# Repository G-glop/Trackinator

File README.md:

# Todo

- [X] Put Obsidian notes inside the repo
- [X] Add a README.md
- [x] Search the calendar for any Trackinator info and add it here
	- [x] select the flex connector & crystals & oscillators (to free up browser tabs)
	- [x] transfer my eyetrack diagram to kicad (don't worry about simple component values/choices)
	- [x] abandon fully flex design and opt into frunkable + flex illuminators / extensions
	- [ ] drive all ir leds from a single current limited source to ensure sum i <= safe limit
- [ ] M.2 like half screw-hole for mounting in a custom frunk housing
- [x] Import new FFC connector
- FCC connector orientaion:
	- Face cams prefer pins up
	- Eye and nose cams prefer pins down
- [ ] Place the hub indicator LEDs close to their respective ESP/downstream port
- [ ] ESP UART output headers
- [x] Remove `fp-info-cache` from the repo and ignore it
- [x] Add camera pinout to it
	- Did the option with least fewest crossing lines, could've copied the xiao but eh
- [ ] Symmetrize all the connectors and lock them
- [x] Select and add USB C and A female connectors
  - [ ] What does a USB C host port need in addition to P+N+5V+GND?
- [x] 3D print the outline + USB A + FFC connectors to check the fit
- [ ] Switch KiCad to JLCPCB 4+ layer capabilites (I'm gonna need them)
- [ ] Use painters tape + scanner + 3d printer to prototype a flex PCB (or 3D scan / manally model the index)
  - [ ] IR illumination
  - [ ] Ambilight
  - [ ] Reuse the 24P FFC connector
	  - Either look at the [camera mechanical drawings](https://www.aliexpress.com/item/1005003906449317.html?spm=a2g0o.order_list.order_list_main.10.361c1802tWpc3p) or at the [FFC connector datasheet](https://datasheet.lcsc.com/lcsc/2001071406_XFCN-F0503-ZV-24-20T-R_C481246.pdf)
- [ ] Add headers as an alternative to the flex PCB + FFC connector
- [x] Add a few ERM drivers
	- [ ] If i run out of space, replace some of the RS485 drivers with N mosefts
- [x] Move tasks from the system diagram here
	- Flex PCB hatching instead of solid pours provide better flexibility but shouldn't be used with high frequency. Use denser hatching if possible
	- [ ] ESPs connected to a shared bus (I2C?) for sidechannel communication
	- [ ] Strapping pins so each ESP can tell where it is (or voltage divider on an ADC pin)
	- [x] Shared RESET and GPIO0 signals connected to buttons
	- [ ] Series JTAG for the hell of it
		- The ESP has built in USB JTAG already and the xiaos don't have it either, so leave it out for more pins?
	- [x] PWM + Tacho PC fan header (commodity PC fans run at 12 V and usually require at least 7 V to start - do i need a boost converter?)
		- [ ] Add 5V/ground switching in addition to PWM to be safe
		- [ ] (maybe) add some option of a 12V boost converter
	- [ ] Make a few recordings to try out how much of an impact the dead cats make on audio - they're right in the space for mouth tracking cameras
- [ ] Add good quality voltage sources (switch mode where applicable)
	- [x] Bucks for 3v3 and WS2812B
	- [ ] LDOs for 1v2 and 2v8 camera supplies (low noise)
- [ ] Add a footprint for the google coral AI chip? (G313-06329-00)
	- Needs usb + power + space for all the ground pins
	- Or use the M.2 PCIe version(s) and stuff it into the PC
- [ ] Add thermal vias under the ESPs
- [ ] (meme) composite all 5 camera feeds together into a cursed webcam - "vision pro without ai"
- [x] Align the USB A male 3d model with footprint
	- [x] Same for the buck module
- [ ] Use the "Round Tracks" plugin from mixtela together with via/pad teardrops
	- It's an actual benefit on flex PCBs
- [ ] The flex PCBs of the cameras seem to have some intentional engineering compared to "bunch of parallel tracks" like a FFC cable.
- Add logos:
	- [ ] EyeTrackVR
	- [ ] OpenSourceHW
	- [ ] G_glop
- [ ] Add an automatically updating "Exported at \[date] \[tag] \[branch] \[commit #]" text
	- Date is easy using the ${CURRENT_DATE} variable
- LCSC Order:
	- [x] USB connector
	- [x] Fan headers
	- [ ] IR Leds
	- [ ] Trim pot to tune WS2812B supply voltage
- [ ] Export a 3D model of the board and make it into a VRChat world with the top & bottom (copper + mask + silkscreen) are the ceiling & floor, and vias are columns between the two (scale correct?)
	- The VRML export is fine (imports into Blender) but everything is geometry, use it only for vias and export everything else as SVG (later rasterzied)?
	- There're no gradients and sharp edges are greatly reduced by using teardrops, mSDF(s) could be a better choice than an RGB texture.
		- https://github.com/Chlumsky/msdfgen (only accepts SVG - use Plot in KiCad)
		- (a) 2 mSDFs selecting between 3 colors
		- (b) 1 mSDF selecting between 2 textures
		- or (c) quantize the interpolated RGB value back to one of the 3 colors
	- Rave mode which shows the frequency and direction of signal on each trace.
		- SDFs could be useful for outlines

Notes:
	Command to download LCSC/EasyEDA footprint: `easyeda2kicad --full --lcsc_id [Cxxxx]`

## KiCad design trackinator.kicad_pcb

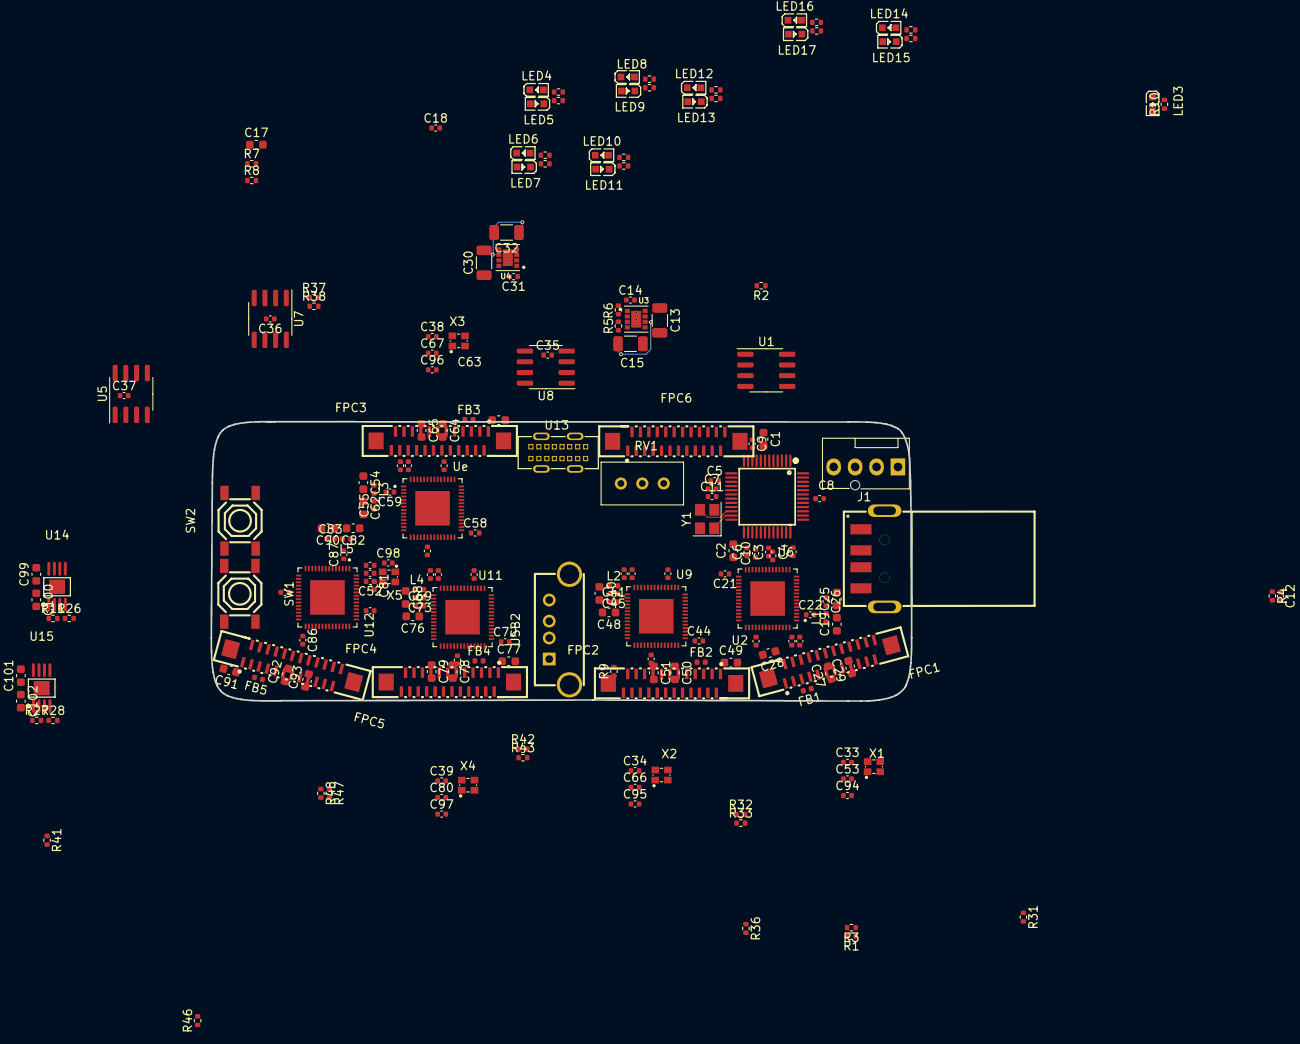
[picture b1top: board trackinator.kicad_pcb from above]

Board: 4 copper layers, 83.0 x 33.1 mm, 200 parts (0 on the bottom side), 160 nets.

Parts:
C1, C2, C17, C19, C25, C27, C28, C29, C40, C48, C49, C50, C51, C54, C62, C63, C64, C65, C68, C76, C77, C78, C79, C82, C90, C91, C92, C93, C99, C100, C101, C102: 10u; C_0603_1608Metric
C3, C4, C5, C6, C7, C8, C9, C10, C11, C12, C16, C18, C20, C21, C22, C23, C24, C26, C35, C36, C37, C41, C42, C43, C44, C45, C46, C47, C55, C56, C57, C58, C59, C60, C61, C69, C70, C71, C72, C73, C74, C75, C83, C84, C85, C86, C87, C88, C89, C94, C95, C96, C97, C98: 100n; C_0402_1005Metric
C13, C15, C30, C32: 22u; C_1206_3216Metric
C14, C31: 3300p; C_0402_1005Metric
C33, C34, C38, C39, C52, C53, C66, C67, C80, C81: 100p; C_0402_1005Metric
FB1, FB2, FB3, FB4, FB5: 100R-800mA; L_0402_1005Metric
FPC1, FPC2, FPC3, FPC4, FPC5, FPC6: F0503-ZV-24-20T-R; FPC-SMD_F0503-ZV-24-20T-R
J1: Conn_01x04_Pin; FanPinHeader_1x04_P2.54mm_Vertical
L1, L2, L3, L4, L5: 3n9; L_0402_1005Metric
LED3: RED; LED0603-RD
LED4, LED6, LED8, LED10, LED12, LED14, LED16: YELLOW; LED0603-RD-YELLOW
LED5, LED7, LED9, LED11, LED13, LED15, LED17: GREEN; LED0603-RD
R1, R3, R32, R33, R37, R38, R42, R43, R47, R48: 4k7; R_0402_1005Metric
R2: 2k7; R_0402_1005Metric
R4, R7, R8: 10k; R_0402_1005Metric
R5: 1M21; R_0402_1005Metric
R6: 383k; R_0402_1005Metric
R9, R10, R12, R13, R14, R15, R16, R17, R18, R19, R20, R21, R22, R23, R24, R25, R31, R36, R41, R46: 1k; R_0402_1005Metric
R11, R26, R27, R28: tbd; R_0402_1005Metric
RV1: 50k; Potentiometer_Bourns_3296W_Vertical
SW1, SW2: TS-1187A-B-A-B; SW-SMD_4P-L5.1-W5.1-P3.70-LS6.5-TL-2
U1: M24C02-WMN; SOIC-8_3.9x4.9mm_P1.27mm
U2, U9, U11, U12: ESP32-S3FH4R2
U3, U4: LMZ21701SILR; CONV_TPS82140SILR
U5, U7, U8: SP3481EN; SOIC-8_3.9x4.9mm_P1.27mm
U6: FE2.1; LQFP-48_L7.0-W7.0-P0.50-LS9.0-BL
U13: TYPE-C 16PLC-H10.0; TYPE-C-TH_16PLC-H10.0
U14, U15: ADP125ARHZ-R7; MSOP-8_L3.0-W3.0-P0.65-LS4.9-BL-EP
USB1: U217-04XN-XXR84; USB-A-SMD_U217-041N-4BV81
USB2: 1734366-1; USB-A-TH_FUS264-FDSW3K
Ue: ESP32-S3FH4R2
X1, X2, X3, X4, X5: 40Mhz; OSC-SMD_4P-L2.0-W1.6-BL_SIT1602BI
Y1: 12Mhz; Crystal_SMD_3225-4Pin_3.2x2.5mm

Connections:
+3V3: C3.2, C4.2, C5.2, C6.2, C7.2, C8.2, C15.1, C16.1, C18.2, C19.1, C20.1, C23.1, C24.1, C40.1, C42.1, C43.1, C46.1, C47.1, C54.1, C56.1, C57.1, C60.1, C61.1, C68.1, C70.1, C71.1, C74.1, C75.1, C82.1, C84.1, C85.1, C88.1, C89.1, C94.2, C95.2, C96.2, C97.2, C98.2, C99.2, C101.2, L1.1, L2.1, L3.1, L4.1, L5.1, R4.1, R5.1, R7.2, R8.2, U1.8 (VCC), U2.20 (VDD3P3_RTC), U2.46 (VDD3P3_CPU), U2.55 (VDDA1), U2.56 (VDDA2), U3.4 (VOUT), U3.6 (VOS), U6.15 (VD33), U6.20 (VD33), U6.26 (VD33), U6.31 (VD33), U6.36 (VD33), U6.42 (VD33), U9.20 (VDD3P3_RTC), U9.46 (VDD3P3_CPU), U9.55 (VDDA1), U9.56 (VDDA2), U11.20 (VDD3P3_RTC), U11.46 (VDD3P3_CPU), U11.55 (VDDA1), U11.56 (VDDA2), U12.20 (VDD3P3_RTC), U12.46 (VDD3P3_CPU), U12.55 (VDDA1), U12.56 (VDDA2), U14.5 (EN), U14.7 (VIN), U14.8 (VIN), U15.5 (EN), U15.7 (VIN), U15.8 (VIN), Ue.20 (VDD3P3_RTC), Ue.46 (VDD3P3_CPU), Ue.55 (VDDA1), Ue.56 (VDDA2), X1.1 (TRI), X1.4 (VDD), X2.1 (TRI), X2.4 (VDD), X3.1 (TRI), X3.4 (VDD), X4.1 (TRI), X4.4 (VDD), X5.1 (TRI), X5.4 (VDD)
+5V: C13.1, C30.1, C35.2, C36.2, C37.2, U3.7 (EN), U3.8 (VIN), U4.7 (EN), U4.8 (VIN), U5.8 (VCC), U6.8 (VDD5), U6.41 (VBUSM), U7.8 (VCC), U8.8 (VCC), USB1.1 (VCC)
/Config_LED1/DRV: LED4.1 (C), LED5.2 (A), LED6.1 (C), LED7.2 (A), LED8.1 (C), LED9.2 (A), LED10.1 (C), LED11.2 (A), LED12.1 (C), LED13.2 (A), LED14.1 (C), LED15.2 (A), LED16.1 (C), LED17.2 (A), R10.2, U6.1 (DRV)
/Config_LED2/LED: R14.2, R15.2, U6.4 (LED[2])
/Config_LED3/LED: R16.2, R17.2, U6.5 (LED[3])
/Config_LED4/LED: R18.2, R19.2, U6.7 (LED[4])
/Config_LED5/LED: R20.2, R21.2, U6.48 (LED[5])
/Config_LED6/LED: R22.2, R23.2, U6.47 (LED[6])
/Config_LED7/LED: R24.2, R25.2, U6.46 (LED[7])
/ESP32_1/CAM_PWDN: FPC1.8 (PWDN), U2.23 (GPIO17)
/ESP32_1/CAM_RESET: FPC1.6 (RESET), U2.27 (GPIO21)
/ESP32_1/CAM_SCL: FPC1.5 (SCL), R3.2, U2.38 (GPIO33)
/ESP32_1/CAM_SDA: FPC1.3 (SDA), R1.2, U2.39 (GPIO34)
/ESP32_1/CHIP_PU: C17.2, R8.1, SW2.3 (C), SW2.4 (D), U2.4 (CHIP_PU)
/ESP32_1/DVP_HREF: FPC1.9 (HREF), U2.19 (GPIO14)
/ESP32_1/DVP_PCLK: FPC1.17 (PCLK), U2.14 (GPIO9)
/ESP32_1/DVP_VSYNC: FPC1.7 (VSYNC), U2.24 (GPIO18)
/ESP32_1/DVP_Y2: FPC1.19 (Y2), U2.12 (GPIO7)
/ESP32_1/DVP_Y3: FPC1.21 (Y3), U2.10 (GPIO5)
/ESP32_1/DVP_Y4: FPC1.22 (Y4), U2.9 (GPIO4)
/ESP32_1/DVP_Y5: FPC1.20 (Y5), U2.11 (GPIO6)
/ESP32_1/DVP_Y6: FPC1.18 (Y6), U2.13 (GPIO8)
/ESP32_1/DVP_Y7: FPC1.16 (Y7), U2.15 (GPIO10)
/ESP32_1/DVP_Y8: FPC1.14 (Y8), U2.16 (GPIO11)
/ESP32_1/DVP_Y9: FPC1.12 (Y9), U2.18 (GPIO13)
/ESP32_1/GPIO0: R7.1, SW1.3 (C), SW1.4 (D), U2.5 (GPIO0)
/ESP32_1/USB_DN: U2.25 (GPIO19), U6.11 (DM4)
/ESP32_1/USB_DP: U2.26 (GPIO20), U6.12 (DP4)
/ESP32_1/XMCLK: FPC1.13 (XMCLK), U2.17 (GPIO12)
/ESP32_2/CAM_PWDN: FPC2.8 (PWDN), U9.23 (GPIO17)
/ESP32_2/CAM_RESET: FPC2.6 (RESET), U9.27 (GPIO21)
/ESP32_2/CAM_SCL: FPC2.5 (SCL), R33.2, U9.38 (GPIO33)
/ESP32_2/CAM_SDA: FPC2.3 (SDA), R32.2, U9.39 (GPIO34)
/ESP32_2/DVP_HREF: FPC2.9 (HREF), U9.19 (GPIO14)
/ESP32_2/DVP_PCLK: FPC2.17 (PCLK), U9.14 (GPIO9)
/ESP32_2/DVP_VSYNC: FPC2.7 (VSYNC), U9.24 (GPIO18)
/ESP32_2/DVP_Y2: FPC2.19 (Y2), U9.12 (GPIO7)
/ESP32_2/DVP_Y3: FPC2.21 (Y3), U9.10 (GPIO5)
/ESP32_2/DVP_Y4: FPC2.22 (Y4), U9.9 (GPIO4)
/ESP32_2/DVP_Y5: FPC2.20 (Y5), U9.11 (GPIO6)
/ESP32_2/DVP_Y6: FPC2.18 (Y6), U9.13 (GPIO8)
/ESP32_2/DVP_Y7: FPC2.16 (Y7), U9.15 (GPIO10)
/ESP32_2/DVP_Y8: FPC2.14 (Y8), U9.16 (GPIO11)
/ESP32_2/DVP_Y9: FPC2.12 (Y9), U9.18 (GPIO13)
/ESP32_2/XMCLK: FPC2.13 (XMCLK), U9.17 (GPIO12)
/ESP32_3/CAM_PWDN: FPC3.8 (PWDN), Ue.23 (GPIO17)
/ESP32_3/CAM_RESET: FPC3.6 (RESET), Ue.27 (GPIO21)
/ESP32_3/CAM_SCL: FPC3.5 (SCL), R38.2, Ue.38 (GPIO33)
/ESP32_3/CAM_SDA: FPC3.3 (SDA), R37.2, Ue.39 (GPIO34)
/ESP32_3/DVP_HREF: FPC3.9 (HREF), Ue.19 (GPIO14)
/ESP32_3/DVP_PCLK: FPC3.17 (PCLK), Ue.14 (GPIO9)
/ESP32_3/DVP_VSYNC: FPC3.7 (VSYNC), Ue.24 (GPIO18)
/ESP32_3/DVP_Y2: FPC3.19 (Y2), Ue.12 (GPIO7)
/ESP32_3/DVP_Y3: FPC3.21 (Y3), Ue.10 (GPIO5)
/ESP32_3/DVP_Y4: FPC3.22 (Y4), Ue.9 (GPIO4)
/ESP32_3/DVP_Y5: FPC3.20 (Y5), Ue.11 (GPIO6)
/ESP32_3/DVP_Y6: FPC3.18 (Y6), Ue.13 (GPIO8)
/ESP32_3/DVP_Y7: FPC3.16 (Y7), Ue.15 (GPIO10)
/ESP32_3/DVP_Y8: FPC3.14 (Y8), Ue.16 (GPIO11)
/ESP32_3/DVP_Y9: FPC3.12 (Y9), Ue.18 (GPIO13)
/ESP32_3/XMCLK: FPC3.13 (XMCLK), Ue.17 (GPIO12)
/ESP32_4/CAM_PWDN: FPC4.8 (PWDN), U11.23 (GPIO17)
/ESP32_4/CAM_RESET: FPC4.6 (RESET), U11.27 (GPIO21)
/ESP32_4/CAM_SCL: FPC4.5 (SCL), R43.2, U11.38 (GPIO33)
/ESP32_4/CAM_SDA: FPC4.3 (SDA), R42.2, U11.39 (GPIO34)
/ESP32_4/DVP_HREF: FPC4.9 (HREF), U11.19 (GPIO14)
/ESP32_4/DVP_PCLK: FPC4.17 (PCLK), U11.14 (GPIO9)
/ESP32_4/DVP_VSYNC: FPC4.7 (VSYNC), U11.24 (GPIO18)
/ESP32_4/DVP_Y2: FPC4.19 (Y2), U11.12 (GPIO7)
/ESP32_4/DVP_Y3: FPC4.21 (Y3), U11.10 (GPIO5)
/ESP32_4/DVP_Y4: FPC4.22 (Y4), U11.9 (GPIO4)
/ESP32_4/DVP_Y5: FPC4.20 (Y5), U11.11 (GPIO6)
/ESP32_4/DVP_Y6: FPC4.18 (Y6), U11.13 (GPIO8)
/ESP32_4/DVP_Y7: FPC4.16 (Y7), U11.15 (GPIO10)
/ESP32_4/DVP_Y8: FPC4.14 (Y8), U11.16 (GPIO11)
/ESP32_4/DVP_Y9: FPC4.12 (Y9), U11.18 (GPIO13)
/ESP32_4/XMCLK: FPC4.13 (XMCLK), U11.17 (GPIO12)
/ESP32_5/CAM_PWDN: FPC5.8 (PWDN), U12.23 (GPIO17)
/ESP32_5/CAM_RESET: FPC5.6 (RESET), U12.27 (GPIO21)
/ESP32_5/CAM_SCL: FPC5.5 (SCL), R48.2, U12.38 (GPIO33)
/ESP32_5/CAM_SDA: FPC5.3 (SDA), R47.2, U12.39 (GPIO34)
/ESP32_5/DVP_HREF: FPC5.9 (HREF), U12.19 (GPIO14)
/ESP32_5/DVP_PCLK: FPC5.17 (PCLK), U12.14 (GPIO9)
/ESP32_5/DVP_VSYNC: FPC5.7 (VSYNC), U12.24 (GPIO18)
/ESP32_5/DVP_Y2: FPC5.19 (Y2), U12.12 (GPIO7)
/ESP32_5/DVP_Y3: FPC5.21 (Y3), U12.10 (GPIO5)
/ESP32_5/DVP_Y4: FPC5.22 (Y4), U12.9 (GPIO4)
/ESP32_5/DVP_Y5: FPC5.20 (Y5), U12.11 (GPIO6)
/ESP32_5/DVP_Y6: FPC5.18 (Y6), U12.13 (GPIO8)
/ESP32_5/DVP_Y7: FPC5.16 (Y7), U12.15 (GPIO10)
/ESP32_5/DVP_Y8: FPC5.14 (Y8), U12.16 (GPIO11)
/ESP32_5/DVP_Y9: FPC5.12 (Y9), U12.18 (GPIO13)
/ESP32_5/XMCLK: FPC5.13 (XMCLK), U12.17 (GPIO12)
/HUB_SCL: R12.2, R13.2, U1.6 (SCL), U6.3 (LED[1])
/HUB_SDA: U1.5 (SDA), U6.2 (TESTJ)
GND: C1.1, C2.1, C3.1, C4.1, C5.1, C6.1, C7.1, C8.1, C9.1, C10.1, C11.1, C12.1, C13.2, C14.2, C15.2, C16.2, C17.1, C18.1, C19.2, C20.2, C21.2, C22.2, C23.2, C24.2, C25.2, C26.1, C27.2, C29.2, C30.2, C31.2, C32.2, C35.1, C36.1, C37.1, C40.2, C41.1, C42.2, C43.2, C44.2, C45.2, C46.2, C47.2, C48.2, C50.2, C51.2, C54.2, C55.1, C56.2, C57.2, C58.2, C59.2, C60.2, C61.2, C62.2, C64.2, C65.2, C68.2, C69.1, C70.2, C71.2, C72.2, C73.2, C74.2, C75.2, C76.2, C78.2, C79.2, C82.2, C83.1, C84.2, C85.2, C86.2, C87.2, C88.2, C89.2, C90.2, C92.2, C93.2, C94.1, C95.1, C96.1, C97.1, C98.1, C99.1, C100.1, C101.1, C102.1, FPC1.15 (DGND), FPC1.25 (GND), FPC1.26 (GND), FPC2.15 (DGND), FPC2.25 (GND), FPC2.26 (GND), FPC3.15 (DGND), FPC3.25 (GND), FPC3.26 (GND), FPC4.15 (DGND), FPC4.25 (GND), FPC4.26 (GND), FPC5.15 (DGND), FPC5.25 (GND), FPC5.26 (GND), LED3.1 (K), R2.1, R6.2, R13.1, R15.1, R17.1, R19.1, R21.1, R23.1, R25.1, R26.2, R28.2, RV1.1, SW1.1 (A), SW1.2 (B), SW2.1 (A), SW2.2 (B), U1.1 (E0), U1.2 (E1), U1.3 (E2), U1.4 (VSS), U1.7 (~WC), U3.5 (GND), U3.9 (EXP), U3.10 (EXP), U4.5 (GND), U4.9 (EXP), U4.10 (EXP), U5.5 (GND), U6.10 (VSS), U6.24 (VS_PLL), U6.39 (VSS), U7.5 (GND), U8.5 (GND), U14.4 (GND), U14.9 (PAD), U15.4 (GND), U15.9 (PAD), USB1.4 (GND), USB1.5, USB1.6, X1.2 (GND), X2.2 (GND), X3.2 (GND), X4.2 (GND), X5.2 (GND), Y1.2, Y1.4
GNDA: C28.2, C49.2, C63.2, C77.2, C91.2, FPC1.2 (AGND), FPC2.2 (AGND), FPC3.2 (AGND), FPC4.2 (AGND), FPC5.2 (AGND)
unnamed: C22.1, C25.1, C26.2, L1.2, U2.2 (VDD3P3), U2.3 (VDD3P3)
unnamed: C41.2, C45.1, C48.1, L2.2, U9.2 (VDD3P3), U9.3 (VDD3P3)
unnamed: C55.2, C59.1, C62.1, L3.2, Ue.2 (VDD3P3), Ue.3 (VDD3P3)
unnamed: C69.2, C73.1, C76.1, L4.2, U11.2 (VDD3P3), U11.3 (VDD3P3)
unnamed: C83.2, C87.1, C90.1, L5.2, U12.2 (VDD3P3), U12.3 (VDD3P3)
unnamed: C28.1, FB1.2, FPC1.4 (AVDD)
unnamed: C49.1, FB2.2, FPC2.4 (AVDD)
unnamed: C63.1, FB3.2, FPC3.4 (AVDD)
unnamed: C77.1, FB4.2, FPC4.4 (AVDD)
unnamed: C91.1, FB5.2, FPC5.4 (AVDD)
unnamed: LED3.2 (A), R10.1
unnamed: LED4.2 (A), LED5.1 (C), R12.1
unnamed: LED6.2 (A), LED7.1 (C), R14.1
unnamed: LED8.2 (A), LED9.1 (C), R16.1
unnamed: LED10.2 (A), LED11.1 (C), R18.1
unnamed: LED12.2 (A), LED13.1 (C), R20.1
unnamed: LED14.2 (A), LED15.1 (C), R22.1
unnamed: LED16.2 (A), LED17.1 (C), R24.1
unnamed: R9.2, U2.49 (U0TXD)
unnamed: C21.1, U2.29 (VDD_SPI)
unnamed: C53.2, U2.53 (XTAL_N)
unnamed: C33.2, U2.54 (XTAL_P)
unnamed: R5.2, R6.1, U3.2 (FB)
unnamed: C14.1, U3.1 (SS)
unnamed: RV1.2, U4.2 (FB)
unnamed: C31.1, U4.1 (SS)
unnamed: U6.29 (DMU), USB1.2 (D-)
unnamed: U6.30 (DPU), USB1.3 (D+)
unnamed: R2.2, U6.27 (REXT)
unnamed: C1.2, U6.9 (VD33_O)
unnamed: C2.2, C9.2, C10.2, C11.2, U6.6 (VD18), U6.21 (VD_DLL), U6.25 (VDD18_O), U6.28 (VD18)
unnamed: U6.22 (XIN), Y1.3
unnamed: U6.23 (XOUT), Y1.1
unnamed: C12.2, R4.2, U6.40 (XRSTJ)
unnamed: R31.2, U9.49 (U0TXD)
unnamed: C44.1, U9.29 (VDD_SPI)
unnamed: C66.2, U9.53 (XTAL_N)
unnamed: C34.2, U9.54 (XTAL_P)
unnamed: R36.2, Ue.49 (U0TXD)
unnamed: C58.1, Ue.29 (VDD_SPI)
unnamed: C67.2, Ue.53 (XTAL_N)
unnamed: C38.2, Ue.54 (XTAL_P)
unnamed: R41.2, U11.49 (U0TXD)
unnamed: C72.1, U11.29 (VDD_SPI)
unnamed: C80.2, U11.53 (XTAL_N)
unnamed: C39.2, U11.54 (XTAL_P)
unnamed: R46.2, U12.49 (U0TXD)
unnamed: C86.1, U12.29 (VDD_SPI)
unnamed: C81.2, U12.53 (XTAL_N)
unnamed: C52.2, U12.54 (XTAL_P)
unnamed: U13.A1 (GND), U13.A12 (GND), U13.B1 (GND), U13.B12 (GND)
unnamed: U13.A2 (SHIELD), U13.A10 (SHIELD), U13.B2 (SHIELD), U13.B10 (SHIELD)
unnamed: U13.A4 (VBUS), U13.A9 (VBUS), U13.B4 (VBUS), U13.B9 (VBUS)
unnamed: R11.2, R26.1, U14.3 (ADJ)
unnamed: R27.2, R28.1, U15.3 (ADJ)
unnamed: C33.1, C53.1, X1.3 (OUT)
unnamed: C34.1, C66.1, X2.3 (OUT)
unnamed: C38.1, C67.1, X3.3 (OUT)
unnamed: C39.1, C80.1, X4.3 (OUT)
unnamed: C52.1, C81.1, X5.3 (OUT)
VCC_1V2: C29.1, C51.1, C65.1, C79.1, C93.1, C102.2, FPC1.10 (DVDD), FPC2.10 (DVDD), FPC3.10 (DVDD), FPC4.10 (DVDD), FPC5.10 (DVDD), R27.1, U15.1 (VOUT), U15.2 (VOUT)
VCC_2V8: C27.1, C50.1, C64.1, C78.1, C92.1, C100.2, FB1.1, FB2.1, FB3.1, FB4.1, FB5.1, FPC1.11 (DOVDD), FPC2.11 (DOVDD), FPC3.11 (DOVDD), FPC4.11 (DOVDD), FPC5.11 (DOVDD), R1.1, R3.1, R11.1, R32.1, R33.1, R37.1, R38.1, R42.1, R43.1, R47.1, R48.1, U14.1 (VOUT), U14.2 (VOUT)
VDD_WS2812B: C32.1, RV1.3, U4.4 (VOUT), U4.6 (VOS)

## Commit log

2023-07-20 off to a hecking start
2023-07-21 guess this an obsidian vault now
2023-07-26 FFC camera connector + pin mapping
2023-07-27 revving up
2023-07-28 grow todo but also do a lot of work
2023-07-28 crystals and drivers
2023-07-29 ignore fp-info-cache
2023-07-30 more connectors and USB
2023-08-02 savin' my work!
2023-08-04 todo
2023-09-20 readme
